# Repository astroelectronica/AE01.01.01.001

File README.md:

# AE01.01.01.001
ZXCT1080
Voltage output current monitor

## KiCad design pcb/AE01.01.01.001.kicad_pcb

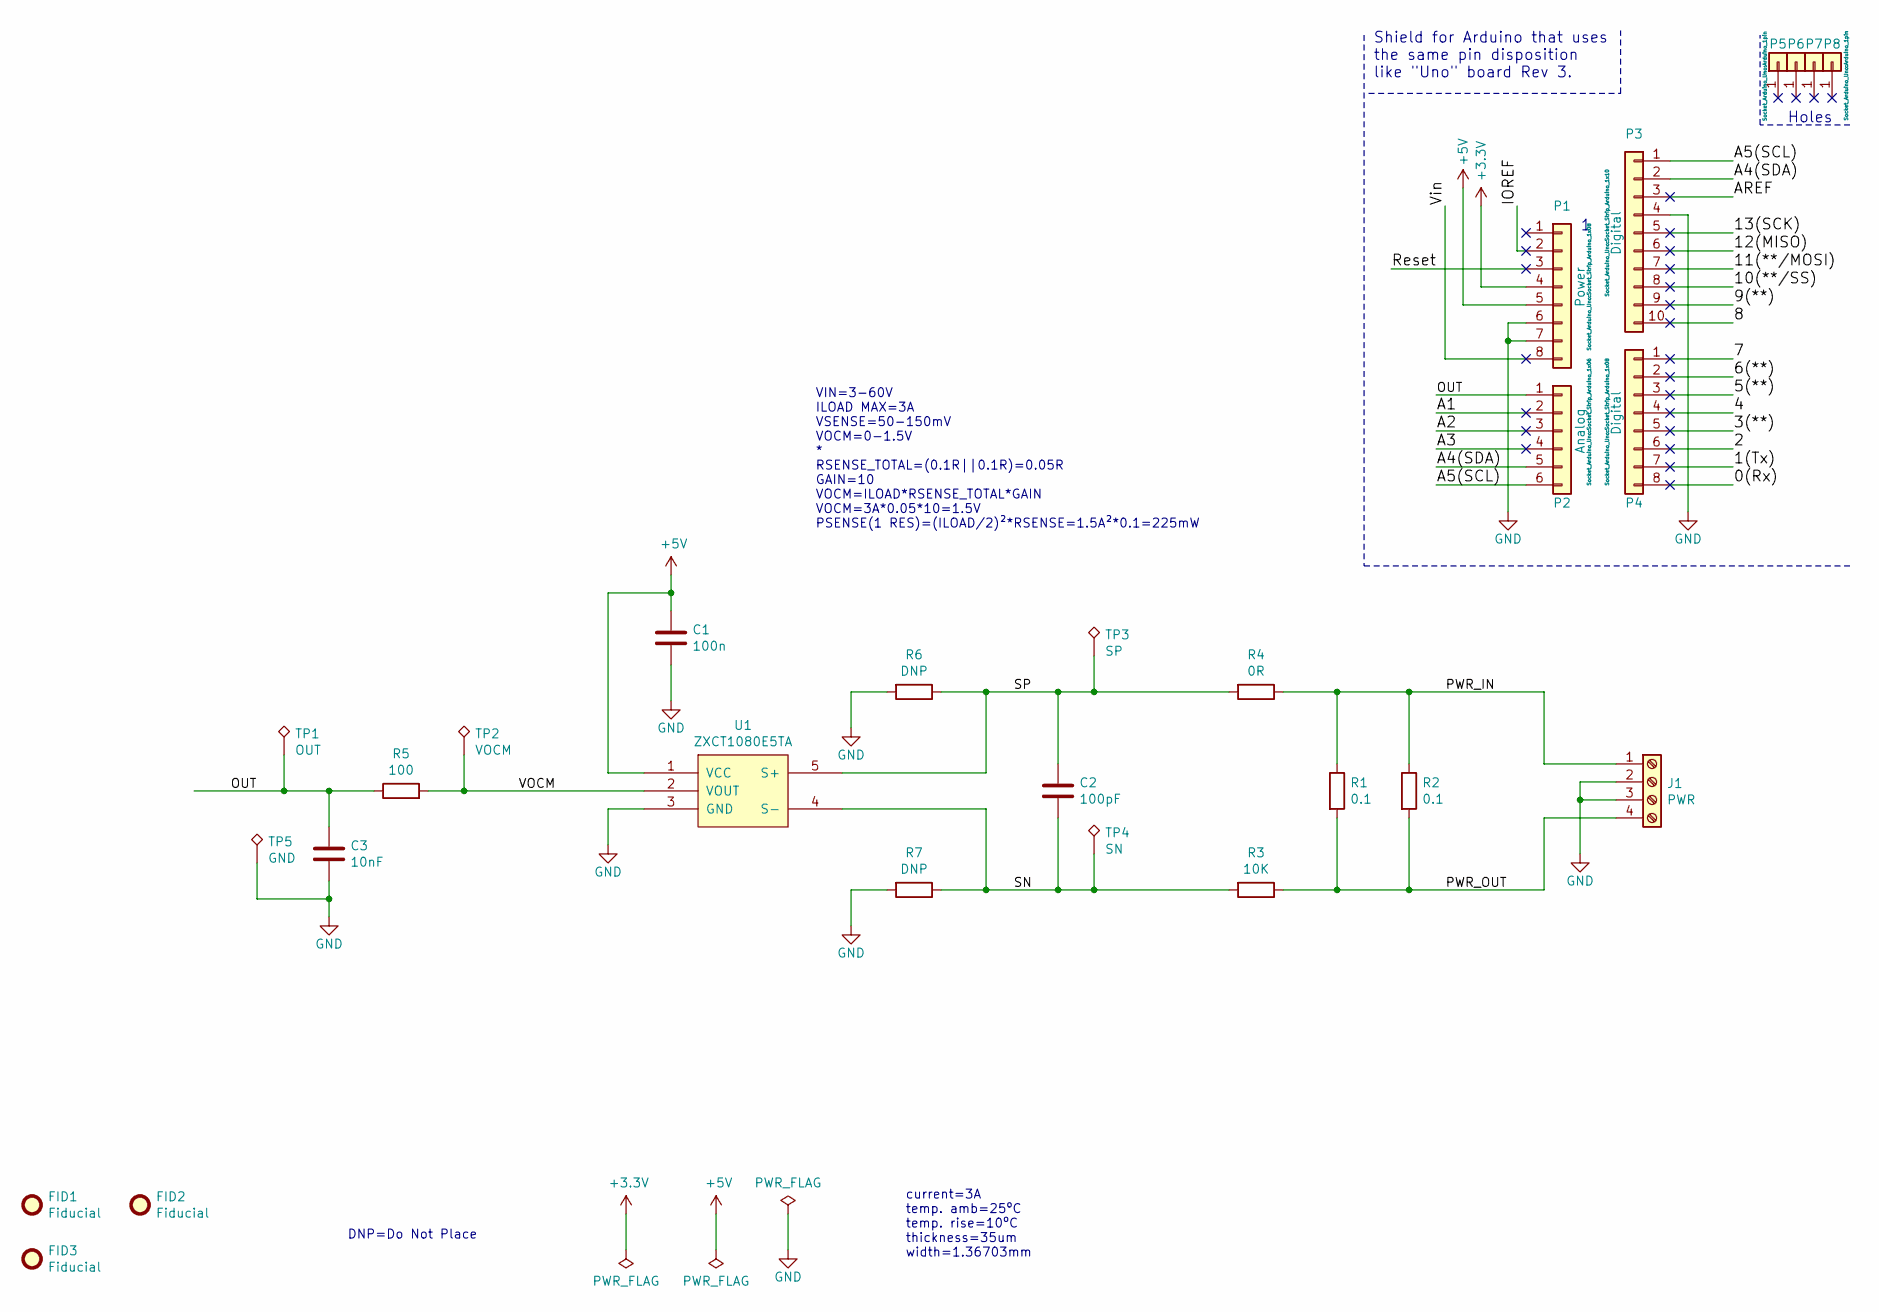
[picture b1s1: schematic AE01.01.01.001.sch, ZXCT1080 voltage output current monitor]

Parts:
C1: 100n; C_0805_2012Metric; MPN C2012X7R2A104K125AA
C2: 100pF; C_0805_2012Metric; MPN C2012CH2W101J060AA
C3: 10nF; C_0805_2012Metric; MPN C2012X7R2E103K125AA
FID1, FID2, FID3: Fiducial; Fiducial_Modern_CopperTop
J1: PWR; TerminalBlock_Phoenix_MKDS-1,5-4-5.08_1x04_P5.08mm_Horizont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; MPN 1715747
P1: Power; Socket_Strip_Arduino_1x08
P2: Analog; Socket_Strip_Arduino_1x06
P3: Digital; Socket_Strip_Arduino_1x10
P4: Digital; Socket_Strip_Arduino_1x08
P5, P6, P7, P8: CONN_01X01; Arduino_1pin
R1, R2: 0.1; R_2512_6332Metric; MPN CRA2512-FZ-R100ELF
R3: 10K; R_0805_2012Metric; MPN RC0805FR-0710KL
R4: 0R; R_0805_2012Metric; MPN RC0805JR-070RL
R5: 100; R_0805_2012Metric; MPN RC0805FR-07100RL
R6, R7: DNP; R_0805_2012Metric
TP1: OUT; TestPoint_Pad_D2.0mm
TP2: VOCM; TestPoint_Pad_D2.0mm
TP3: SP; TestPoint_Pad_D2.0mm
TP4: SN; TestPoint_Pad_D2.0mm
TP5: GND; TestPoint_Pad_D2.0mm
U1: ZXCT1080E5TA; SOT-23-5; MPN ZXCT1080E5TA

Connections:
+3V3: P1.4
+5V: C1.1, P1.5, U1.1 (VCC)
/0(Rx): P4.8
/1(Tx): P4.7
/2: P4.6
/3(**): P4.5
/4: P4.4
/5(**): P4.3
/6(**): P4.2
/7: P4.1
/8: P3.10
/9(**): P3.9
/10(**/SS): P3.8
/11(**/MOSI): P3.7
/12(MISO): P3.6
/13(SCK): P3.5
/A1: P2.2
/A2: P2.3
/A3: P2.4
/A4(SDA): P2.5, P3.2
/A5(SCL): P2.6, P3.1
/AREF: P3.3
/IOREF: P1.2
/OUT: C3.1, P2.1, R5.1, TP1.1
/PWR_IN: J1.1, R1.1, R2.1, R4.1
/PWR_OUT: J1.4, R1.2, R2.2, R3.1
/Reset: P1.3
/SN: C2.2, R3.2, R7.1, TP4.1, U1.4 (S-)
/SP: C2.1, R4.2, R6.1, TP3.1, U1.5 (S+)
/VOCM: R5.2, TP2.1, U1.2 (VOUT)
/Vin: P1.8
GND: C1.2, C3.2, J1.2, J1.3, P1.6, P1.7, P3.4, R6.2, R7.2, TP5.1, U1.3 (GND)

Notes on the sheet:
Holes
Shield for Arduino that uses the same pin disposition like "Uno" board Rev 3.
VIN=3-60V ILOAD MAX=3A VSENSE=50-150mV VOCM=0-1.5V * RSENSE_TOTAL=(0.1R||0.1R)=0.05R GAIN=10 VOCM=ILOAD*RSENSE_TOTAL*GAIN VOCM=3A*0.05*10=1.5V PSENSE(1 RES)=(ILOAD/2)²*RSENSE=1.5A²*0.1=225mW
current=3A temp. amb=25ºC temp. rise=10ºC thickness=35um width=1.36703mm
DNP=Do Not Place

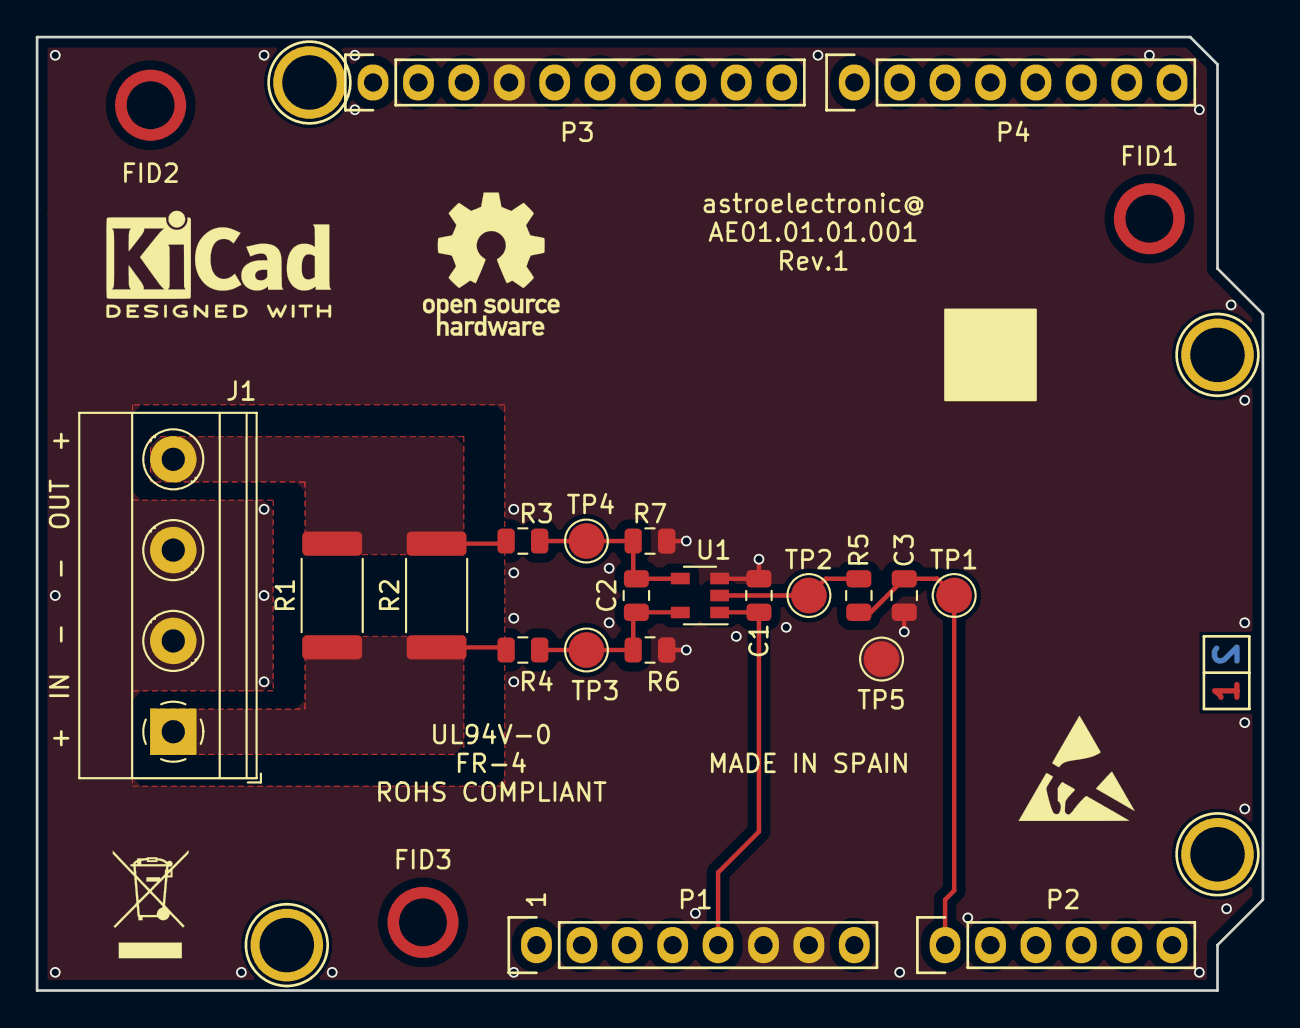
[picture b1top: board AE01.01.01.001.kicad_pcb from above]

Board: 2 copper layers, 68.6 x 53.3 mm, 32 parts (0 on the bottom side), 10 nets.

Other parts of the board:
REF1: KiCad-Logo2_5mm_SilkScreen
REF2: OSHW-Logo_7.5x8mm_SilkScreen
REF3: ESD-Logo_6.6x6mm_SilkScreen
REF4: WEEE-Logo_4.2x6mm_SilkScreen

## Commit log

2021-06-30 Rename readme.md to README.md
